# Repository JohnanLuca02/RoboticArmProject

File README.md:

# RoboticArmProject
Repo for my robotic arm project, to share my PCBs and codes

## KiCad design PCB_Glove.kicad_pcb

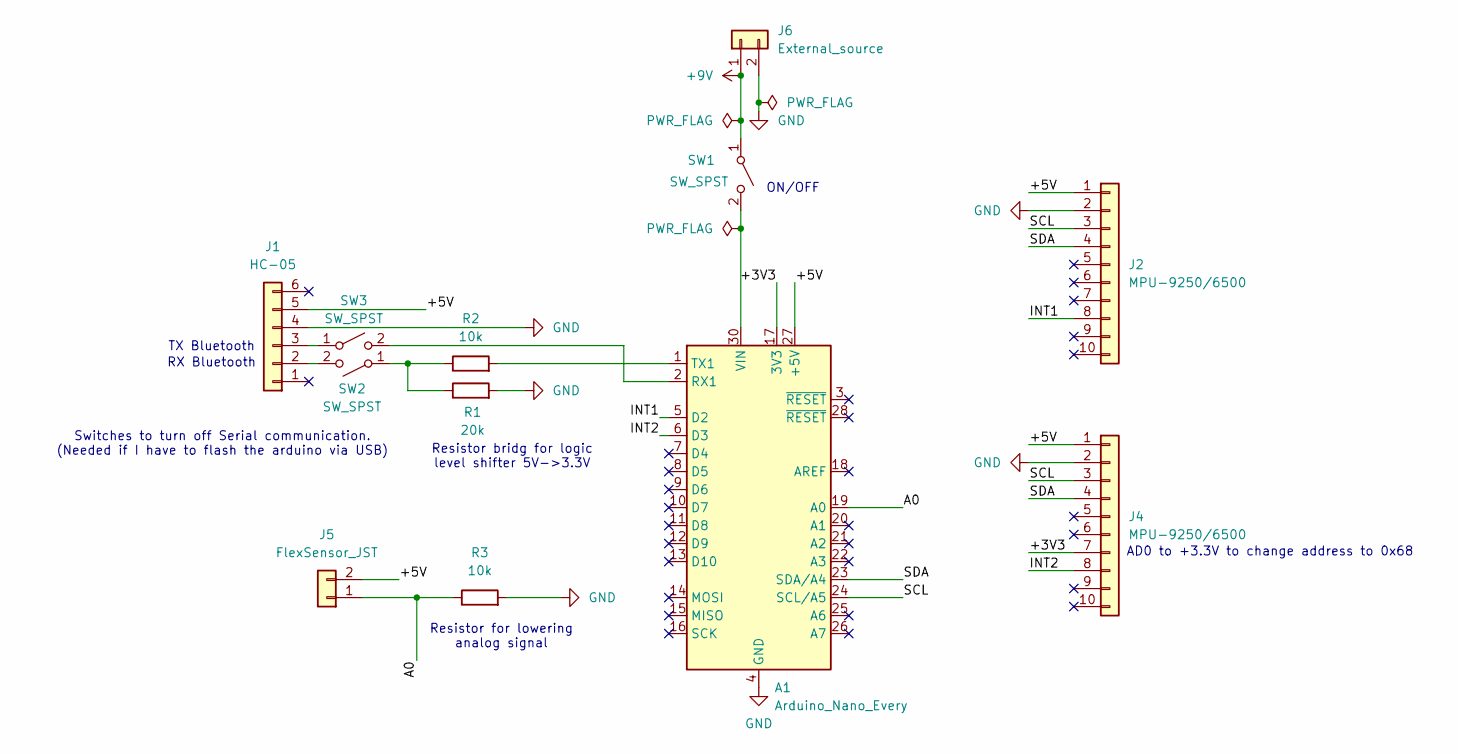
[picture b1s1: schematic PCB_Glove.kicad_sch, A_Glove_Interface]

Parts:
A1: Arduino_Nano_Every; Arduino_Nano
J1: HC-05; PinSocket_1x06_P2.54mm_Vertical
J2, J4: MPU-9250/6500; PinSocket_1x10_P2.54mm_Vertical
J5: FlexSensor_JST; JST_PH_B2B-PH-K_1x02_P2.00mm_Vertical
J6: External_source; JST_PH_B2B-PH-K_1x02_P2.00mm_Vertical
R1: 20k; R_0603_1608Metric
R2, R3: 10k; R_0603_1608Metric
SW1, SW2, SW3: SW_SPST; SW_DIP_SPSTx01_Slide_9.78x4.72mm_W7.62mm_P2.54mm

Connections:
+9V: J6.1, SW1.1 (A)
/+3V3: A1.17 (3V3), J4.7
/+5V: A1.27 (+5V), J1.5, J2.1, J4.1, J5.2
/A0: A1.19 (A0), J5.1, R3.1
/INT1: A1.5 (D2), J2.8
/INT2: A1.6 (D3), J4.8
/SCL: A1.24 (SCL/A5), J2.3, J4.3
/SDA: A1.23 (SDA/A4), J2.4, J4.4
GND: A1.4 (GND), A1.29 (GND), J1.4, J2.2, J4.2, J6.2, R1.2, R3.2
unnamed: A1.2 (RX1), SW3.2 (B)
unnamed: A1.1 (TX1), R2.2
unnamed: A1.30 (VIN), SW1.2 (B)
unnamed: J1.2, SW2.2 (B)
unnamed: J1.3, SW3.1 (A)
unnamed: R1.1, R2.1, SW2.1 (A)

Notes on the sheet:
Resistor for lowering analog signal
AD0 to +3.3V to change address to 0x68
Switches to turn off Serial communication. (Needed if I have to flash the arduino via USB)
ON/OFF
RX Bluetooth
Resistor bridg for logic level shifter 5V->3.3V
TX Bluetooth

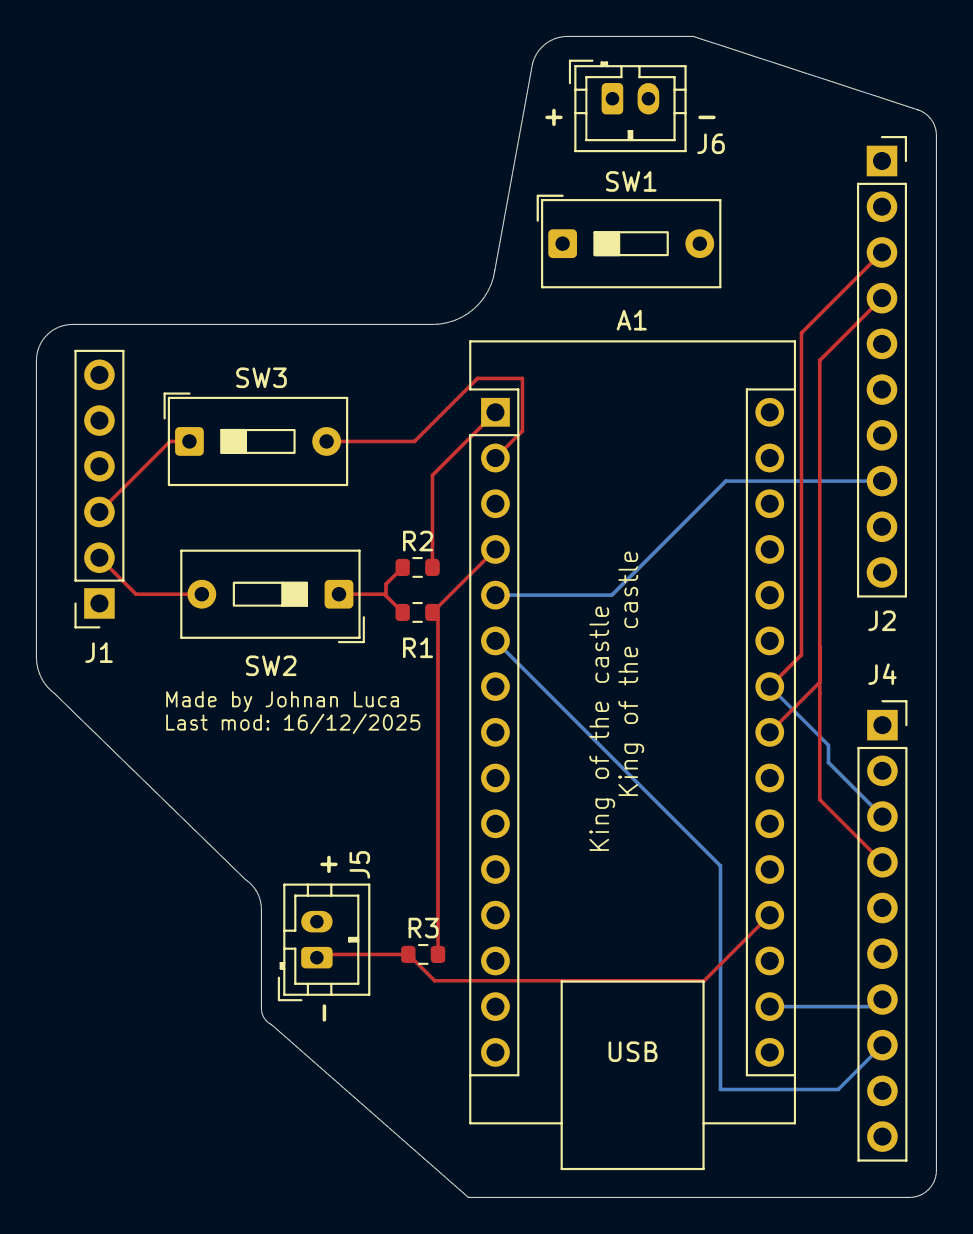
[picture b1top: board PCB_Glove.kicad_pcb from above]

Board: 4 copper layers, 50.0 x 64.5 mm, 12 parts (0 on the bottom side), 15 nets.

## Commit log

2025-12-16 Commit of the folder
2025-12-16 changes in pcb
2025-12-16 Better GND and Edge
2025-12-16 Polished Schematic
